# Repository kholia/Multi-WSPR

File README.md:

Written for 'Pico W' board.

```
[dhiru@zippy Multi-WSPR]$ /usr/bin/wsprd -C 2 -a /home/dhiru/.local/share/WSJT-X -f 14.095600 untight-with-delay-function.wav
tion  26  0.6  14.097030  0  VU3CER MK68 20
<DecodeFinished>
```

```
[dhiru@zippy Multi-WSPR]$ /usr/bin/wsprd -C 2 -a /home/dhiru/.local/share/WSJT-X -f 14.095600 tight-with-busy-loop.wav
loop  26 -0.4  14.097030  0  VU3CER MK68 20
loop -24 -0.3  14.097112  0  VU3CER MK68 20
loop -27 -0.4  14.097193  0  VU3CER MK68 20
<DecodeFinished>
```

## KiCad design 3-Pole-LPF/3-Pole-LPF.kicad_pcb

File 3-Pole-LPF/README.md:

82pf, 7 turns T50-6 220nh and large ground plane -> 40 MHz LPF. Use solid core
enamel wire. Use silver mica caps (56pf + 27pf)!

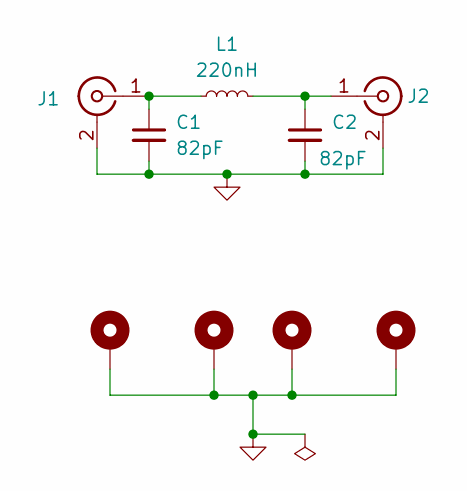
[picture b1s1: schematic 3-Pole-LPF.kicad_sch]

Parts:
C1, C2: 82pF; C_1206_3216Metric_Pad1.33x1.80mm_HandSolder
H1, H2, H3, H4: MountingHole_Pad; MountingHole_2.2mm_M2_Pad
J1, J2: Conn_Coaxial; SMA_Samtec_SMA-J-P-X-ST-EM1_EdgeMount
L1: 220nH; FT50-43 INDUCTOR

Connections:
GND: C1.2, C2.2, H1.1, H2.1, H3.1, H4.1, J1.2 (Ext), J2.2 (Ext)
unnamed: C1.1, J1.1 (In), L1.1
unnamed: C2.1, J2.1 (In), L1.2

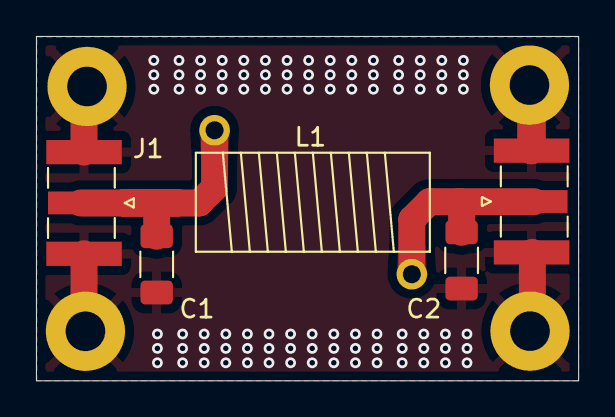
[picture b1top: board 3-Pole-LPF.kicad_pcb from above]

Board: 2 copper layers, 30.1 x 19.1 mm, 9 parts (0 on the bottom side), 3 nets.

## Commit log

2024-03-18 Muti-WSPR PoC
